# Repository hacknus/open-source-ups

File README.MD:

# Open Source UPS

[!CAUTION]
The BOOST circuit in rev 2 cannot provide sufficient current to start a HDD.

UPS are commonly used in server applications to protect against power outages. For home applications, for example to protect a NAS, small Uninterruptible Power Supplies (UPS) do exist, but they all lack the USB HID communication to shut down the NAS/Server/Host when the battery gets low.
For small scale applications like Synology NAS products that operate at 12V, there currently exists no UPS product that is able to buffer the power and communicate over USB when the battery level gets critically low.
Only high voltage solutions (110V or 230V) exist, which also include an inverter and are thus much less efficient and overpowered for a simple 12V Synology NAS.
This is a simple, open source UPS, based around an STM32F405 and written in Rust.

The USB HID communication is based on the great work done by [abratchik](https://github.com/abratchik) for the Arduino platform [here](https://github.com/abratchik/HIDPowerDevice/tree/master). 
The hardware is essentially just a charging circuit where the remaining capacity is monitored by the MCU.

## Hardware
Attention! This pcb does not contain a battery protection circuit - if you wish to implement one, just use the Keystone 1047 battery case instead of the Keystone 1048P and wire a breakout 2S BMS before connecting the batteries to the PCB.
The hardware can be found in the [hardware folder](hardware), containing step files for the case as well as EAGLE files for the PCB.

## Flashing the firmware
Easiest way to flash: Connect via USB-C to your computer. Press RESET and BOOT button on the back of the PCB, release RST first and then release BOOT. The device is now in DFU mode.

Then run the following:
```sh
cargo build --release
/usr/bin/arm-none-eabi-objcopy -O binary   target/thumbv7em-none-eabihf/release/open-source-ups   firmware.bin
dfu-util -l
dfu-util -d 0483:df11 -a 0 \
  -s 0x08000000:leave -D firmware.bin
```

Alternatively:
Connect the board using a ST-Link V3 (with TagConnect) to a USB port on the computer. Be sure to power the board with an
additional USB-C connector. (ST-Link does not provide power)  
First start the openocd server in a terminal/console window:
```openocd -f interface/stlink-v2-1.cfg -f target/stm32f4x.cfg```   
Flash/Run the code on the hardware using:  
```cargo run --release```  
note: release is important for USB to work reliably!

To set up your system, be sure to
follow [this guide](https://docs.rust-embedded.org/discovery/f3discovery/03-setup/index.html)!

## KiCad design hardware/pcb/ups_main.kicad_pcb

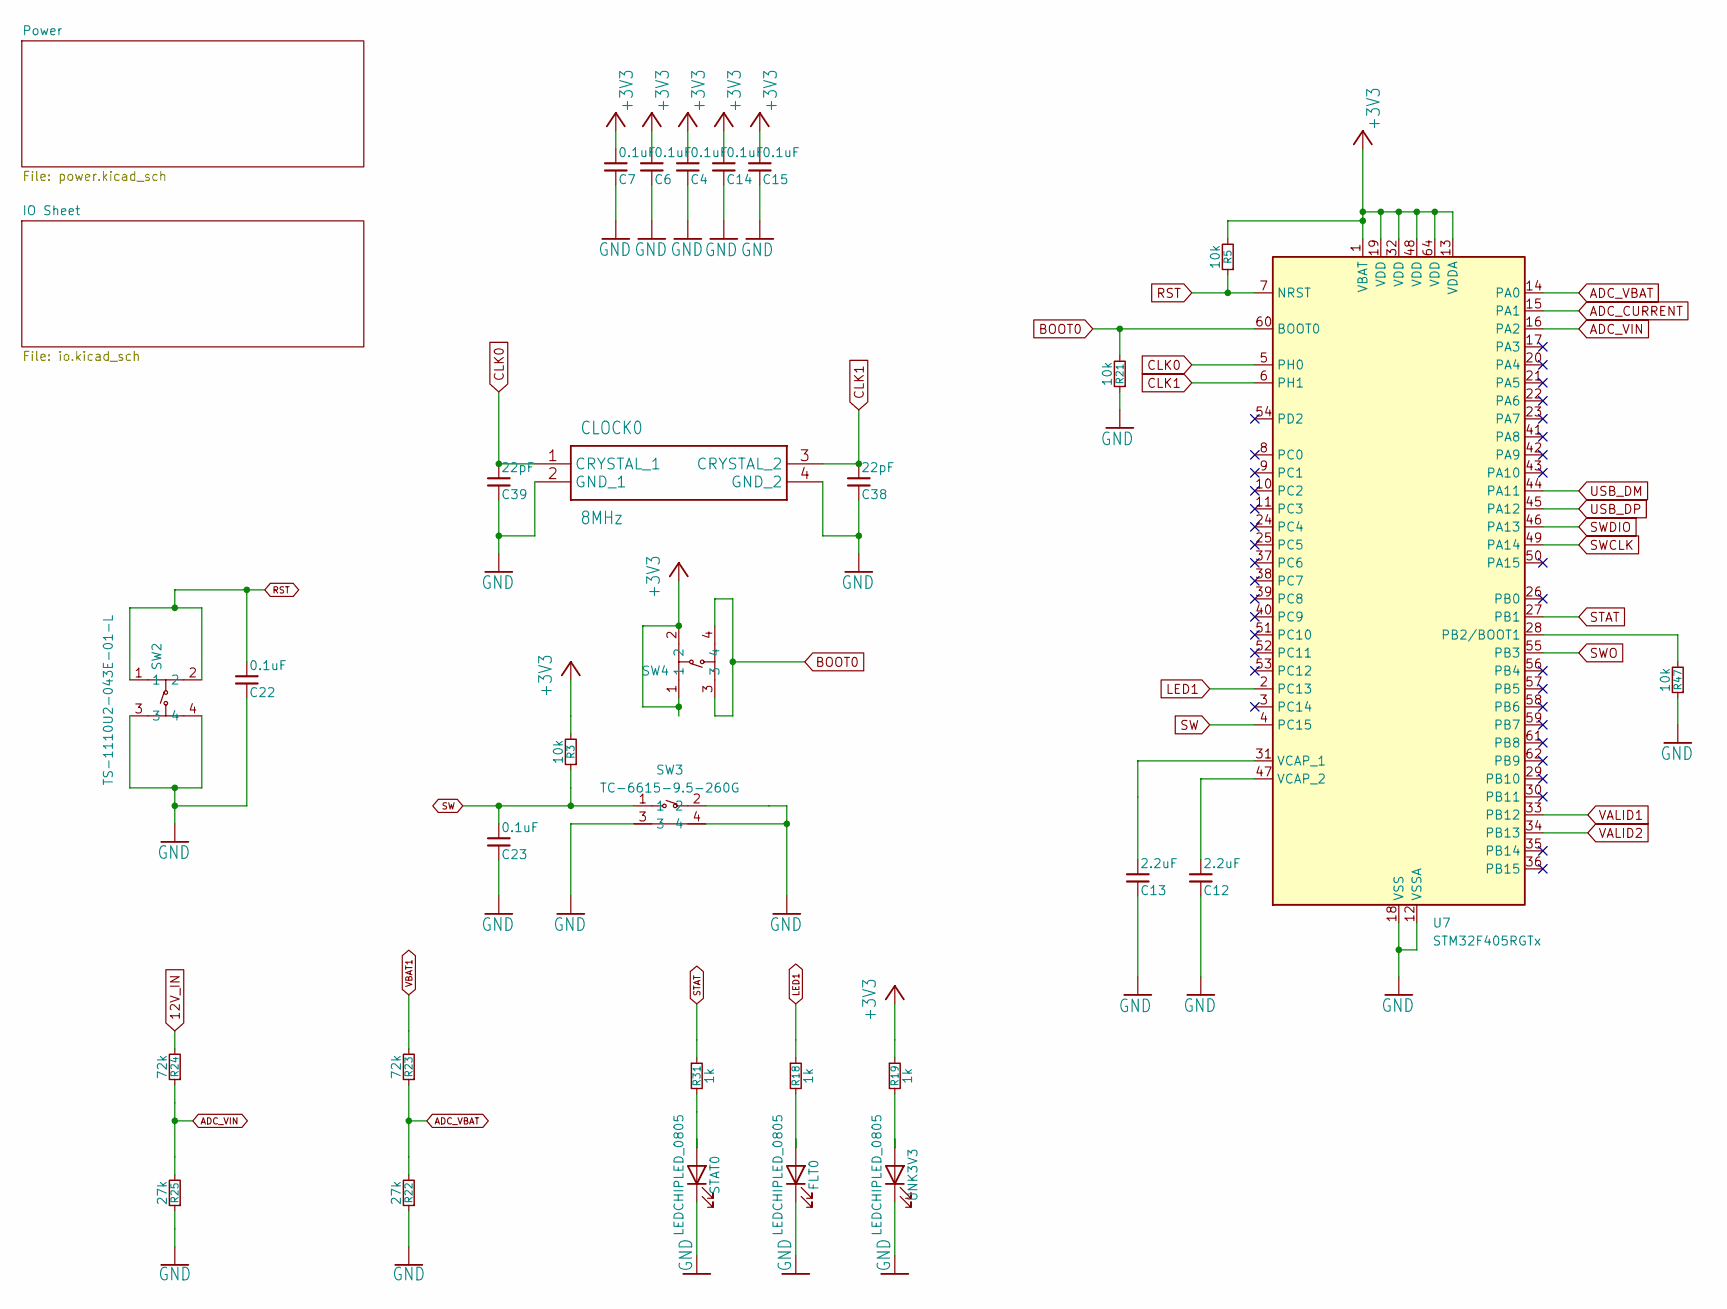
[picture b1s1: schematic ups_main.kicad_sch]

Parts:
C4, C6, C7, C14, C15, C22, C23: 0.1uF; C_0603_1608Metric_Pad1.08x0.95mm_HandSolder
C12, C13: 2.2uF; C_0603_1608Metric_Pad1.08x0.95mm_HandSolder
C38, C39: 22pF; C_0603_1608Metric_Pad1.08x0.95mm_HandSolder
CLOCK0: 8MHz; ABM8AIG8000MHZ1ZT; MANUFACTURER_PART_NUMBER ABM8AIG-8.000MHZ-1Z-T; MOUSER_PART_NUMBER 815-M8AIG-8-1ZT
FLT0: LEDCHIPLED_0805; LED_0805_2012Metric
R3, R5, R21, R47: 10k; R_0603_1608Metric_Pad0.98x0.95mm_HandSolder
R18, R19, R31: 1k; R_0603_1608Metric_Pad0.98x0.95mm_HandSolder
R22, R25: 27k; R_0603_1608Metric_Pad0.98x0.95mm_HandSolder
R23, R24: 72k; R_0603_1608Metric_Pad0.98x0.95mm_HandSolder
STAT0: LEDCHIPLED_0805; LED_0805_2012Metric
SW2, SW4: TS-1110U2-043E-01-L; SW-SMD_4P-L6.5-W6.5-P4.00-LS6.8; MPN TS-1110U2-043E-01-L; LCSC Part C25168654
SW3: TC-6615-9.5-260G; SW-TH_4P-L7.5-W9.5-P4.50; MPN TC-6615-9.5-260G; LCSC Part C2845278
U7: STM32F405RGTx; LQFP-64_10x10mm_P0.5mm
UNK3V3: LEDCHIPLED_0805; LED_0805_2012Metric

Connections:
12V_IN: R24.2; also elsewhere on the board
+3V3: C4.1, C6.1, C7.1, C14.1, C15.1, R3.2, R5.2, R19.1, SW4.1, SW4.2, U7.1 (VBAT), U7.13 (VDDA), U7.19 (VDD), U7.32 (VDD), U7.48 (VDD), U7.64 (VDD); also elsewhere on the board
ADC_CURRENT: U7.15 (PA1); also elsewhere on the board
ADC_VBAT: R22.2, R23.1, U7.14 (PA0)
ADC_VIN: R24.1, R25.2, U7.16 (PA2)
BOOT0: R21.2, SW4.3, SW4.4, U7.60 (BOOT0)
CLK0: C39.1, CLOCK0.1 (CRYSTAL_1), U7.5 (PH0)
CLK1: C38.1, CLOCK0.3 (CRYSTAL_2), U7.6 (PH1)
GND: C4.2, C6.2, C7.2, C12.2, C13.2, C14.2, C15.2, C22.2, C23.2, C38.2, C39.2, CLOCK0.2 (GND_1), CLOCK0.4 (GND_2), FLT0.1 (K), R21.1, R22.1, R25.1, R47.1, STAT0.1 (K), SW2.3, SW2.4, SW3.2, SW3.3, SW3.4, U7.12 (VSSA), U7.18 (VSS), U7.63 (VSS), UNK3V3.1 (K); also elsewhere on the board
LED1: R18.1, U7.2 (PC13)
unnamed: FLT0.2 (A), R18.2
unnamed: R31.2, STAT0.2 (A)
unnamed: R47.2, U7.28 (PB2/BOOT1)
unnamed: C13.1, U7.31 (VCAP_1)
unnamed: C12.1, U7.47 (VCAP_2)
unnamed: R19.2, UNK3V3.2 (A)
RST: C22.1, R5.1, SW2.1, SW2.2, U7.7 (NRST); also elsewhere on the board
STAT: R31.1, U7.27 (PB1)
SW: C23.1, R3.1, SW3.1, U7.4 (PC15)
SWCLK: U7.49 (PA14); also elsewhere on the board
SWDIO: U7.46 (PA13); also elsewhere on the board
SWO: U7.55 (PB3); also elsewhere on the board
USB_DM: U7.44 (PA11); also elsewhere on the board
USB_DP: U7.45 (PA12); also elsewhere on the board
VALID1: U7.33 (PB12); also elsewhere on the board
VALID2: U7.34 (PB13); also elsewhere on the board
VBAT1: R23.2; also elsewhere on the board

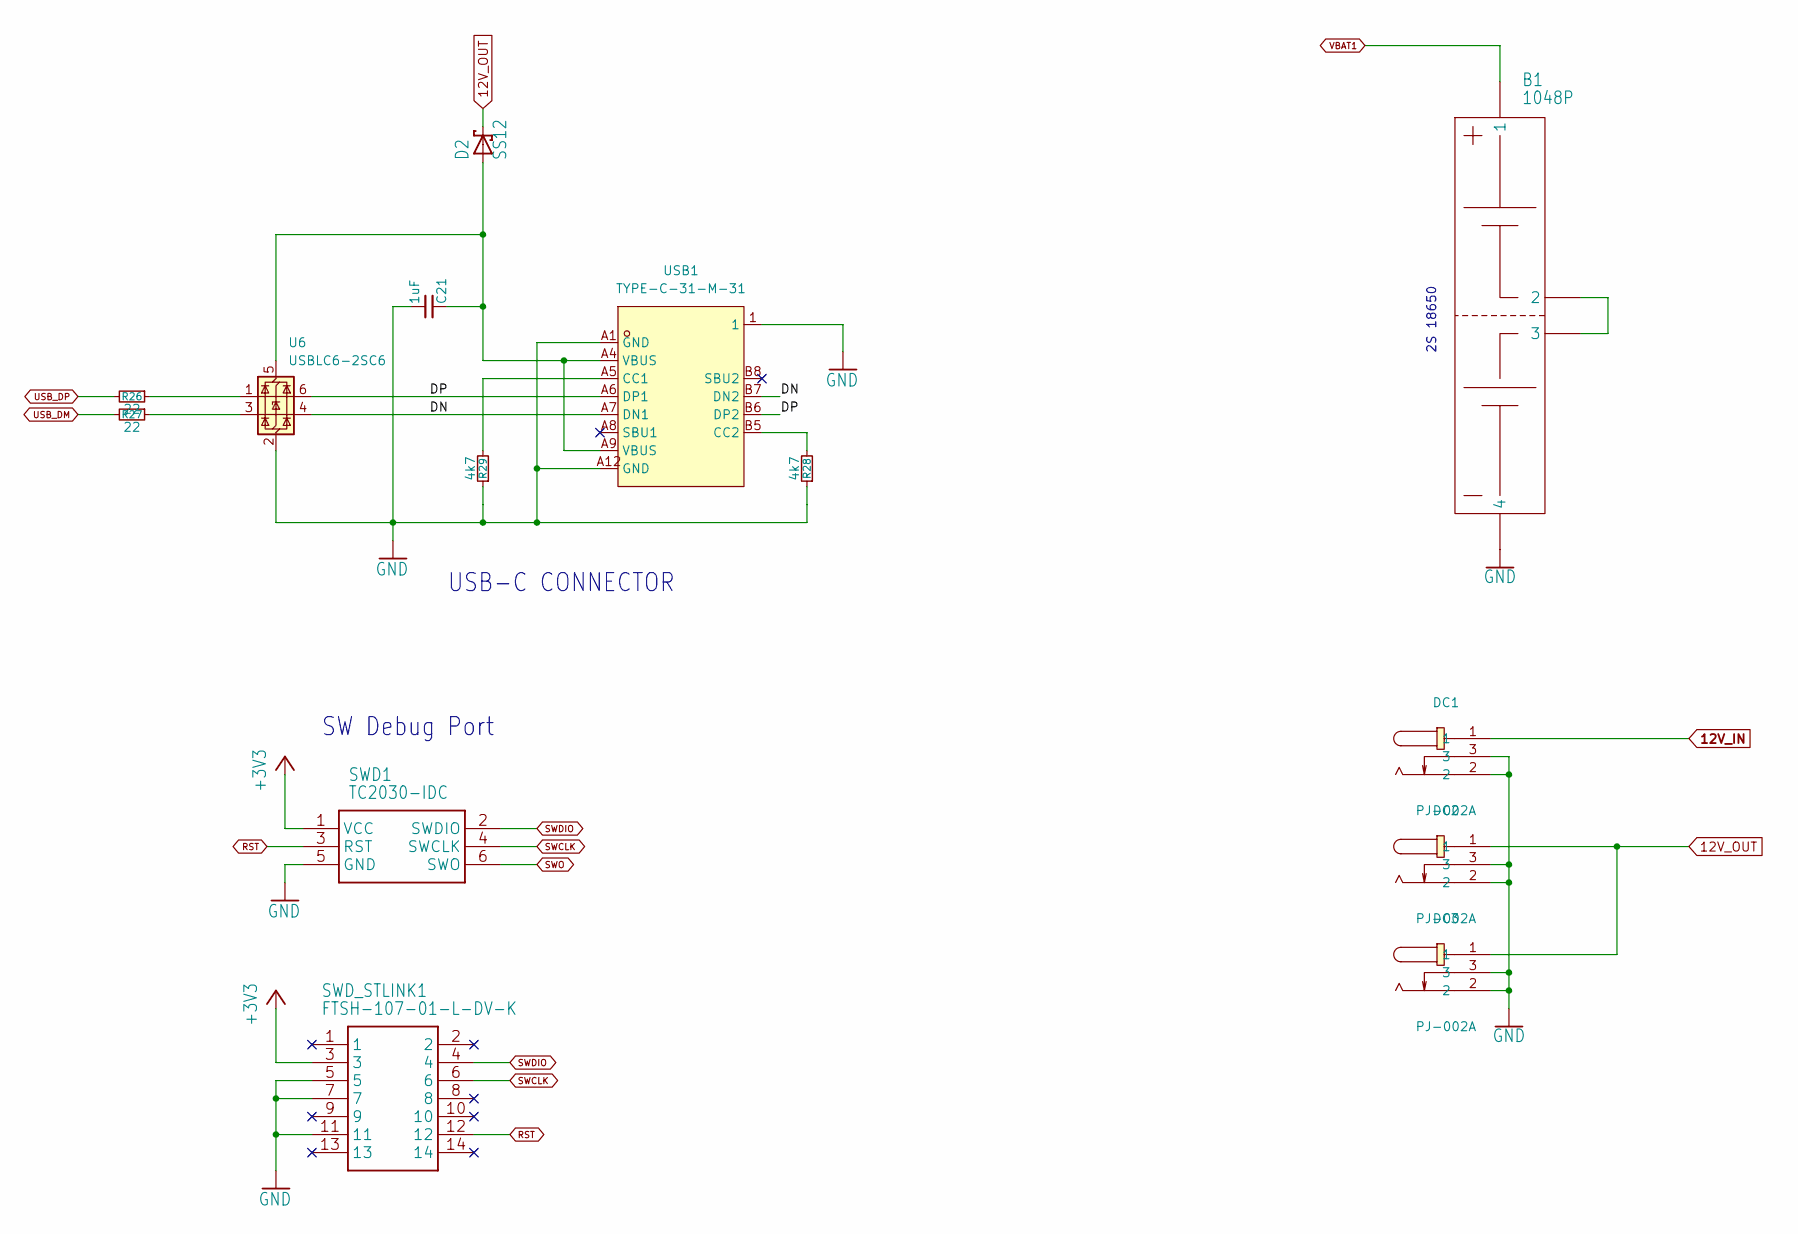
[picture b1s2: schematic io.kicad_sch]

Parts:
B1: 1048P; BATH_KEYSTONE_1048P; MANUFACTURER_PART_NUMBER 1048P; MOUSER_PART_NUMBER 534-1048P
C21: 1uF; C_0603_1608Metric_Pad1.08x0.95mm_HandSolder
D2: SS12; DO214AC
DC1, DC2, DC3: PJ-002A; DC-IN-TH_PJ-002A; MANUFACTURER_PART_NUMBER 694106301002; MOUSER_PART_NUMBER 710-694106301002
R26, R27: 22; R_0603_1608Metric_Pad0.98x0.95mm_HandSolder
R28, R29: 4k7; R_0603_1608Metric_Pad0.98x0.95mm_HandSolder
SWD1: TC2030-IDC; TC2030IDC; MANUFACTURER_PART_NUMBER TC2030-IDC
SWD_STLINK1: FTSH-107-01-L-DV-K; FTSH-107-XX-YYY-DV-K; MANUFACTURER_PART_NUMBER FTSH-107-01-L-DV-K; MOUSER_PART_NUMBER 200-FTSH10701LDVK
U6: USBLC6-2SC6; SOT-23-6
USB1: TYPE-C-31-M-31; USB-C-SMD_TYPE-C-31-M-31; MPN TYPE-C-31-M-31; LCSC Part C2760486

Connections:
12V_IN: DC1.1; also elsewhere on the board
12V_OUT: D2.C, DC2.1, DC3.1; also elsewhere on the board
+3V3: SWD1.1 (VCC), SWD_STLINK1.3; also elsewhere on the board
/IO Sheet/DN: U6.4 (I/O2), USB1.A7 (DN1), USB1.B7 (DN2)
/IO Sheet/DP: U6.6 (I/O1), USB1.A6 (DP1), USB1.B6 (DP2)
GND: B1.4, C21.1, DC1.2, DC1.3, DC2.2, DC2.3, DC3.2, DC3.3, R28.1, R29.1, SWD1.5 (GND), SWD_STLINK1.5, SWD_STLINK1.7, SWD_STLINK1.11, U6.2 (GND), USB1.1, USB1.A1 (GND), USB1.A12 (GND); also elsewhere on the board
unnamed: B1.2, B1.3
unnamed: R26.1, U6.1 (I/O1)
unnamed: R27.1, U6.3 (I/O2)
unnamed: C21.2, D2.A, U6.5 (VBUS), USB1.A4 (VBUS), USB1.A9 (VBUS)
unnamed: R29.2, USB1.A5 (CC1)
unnamed: R28.2, USB1.B5 (CC2)
RST: SWD1.3 (RST), SWD_STLINK1.12; also elsewhere on the board
SWCLK: SWD1.4 (SWCLK), SWD_STLINK1.6; also elsewhere on the board
SWDIO: SWD1.2 (SWDIO), SWD_STLINK1.4; also elsewhere on the board
SWO: SWD1.6 (SWO); also elsewhere on the board
USB_DM: R27.2; also elsewhere on the board
USB_DP: R26.2; also elsewhere on the board
VBAT1: B1.1; also elsewhere on the board

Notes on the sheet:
USB-C CONNECTOR
2S 18650
SW Debug Port

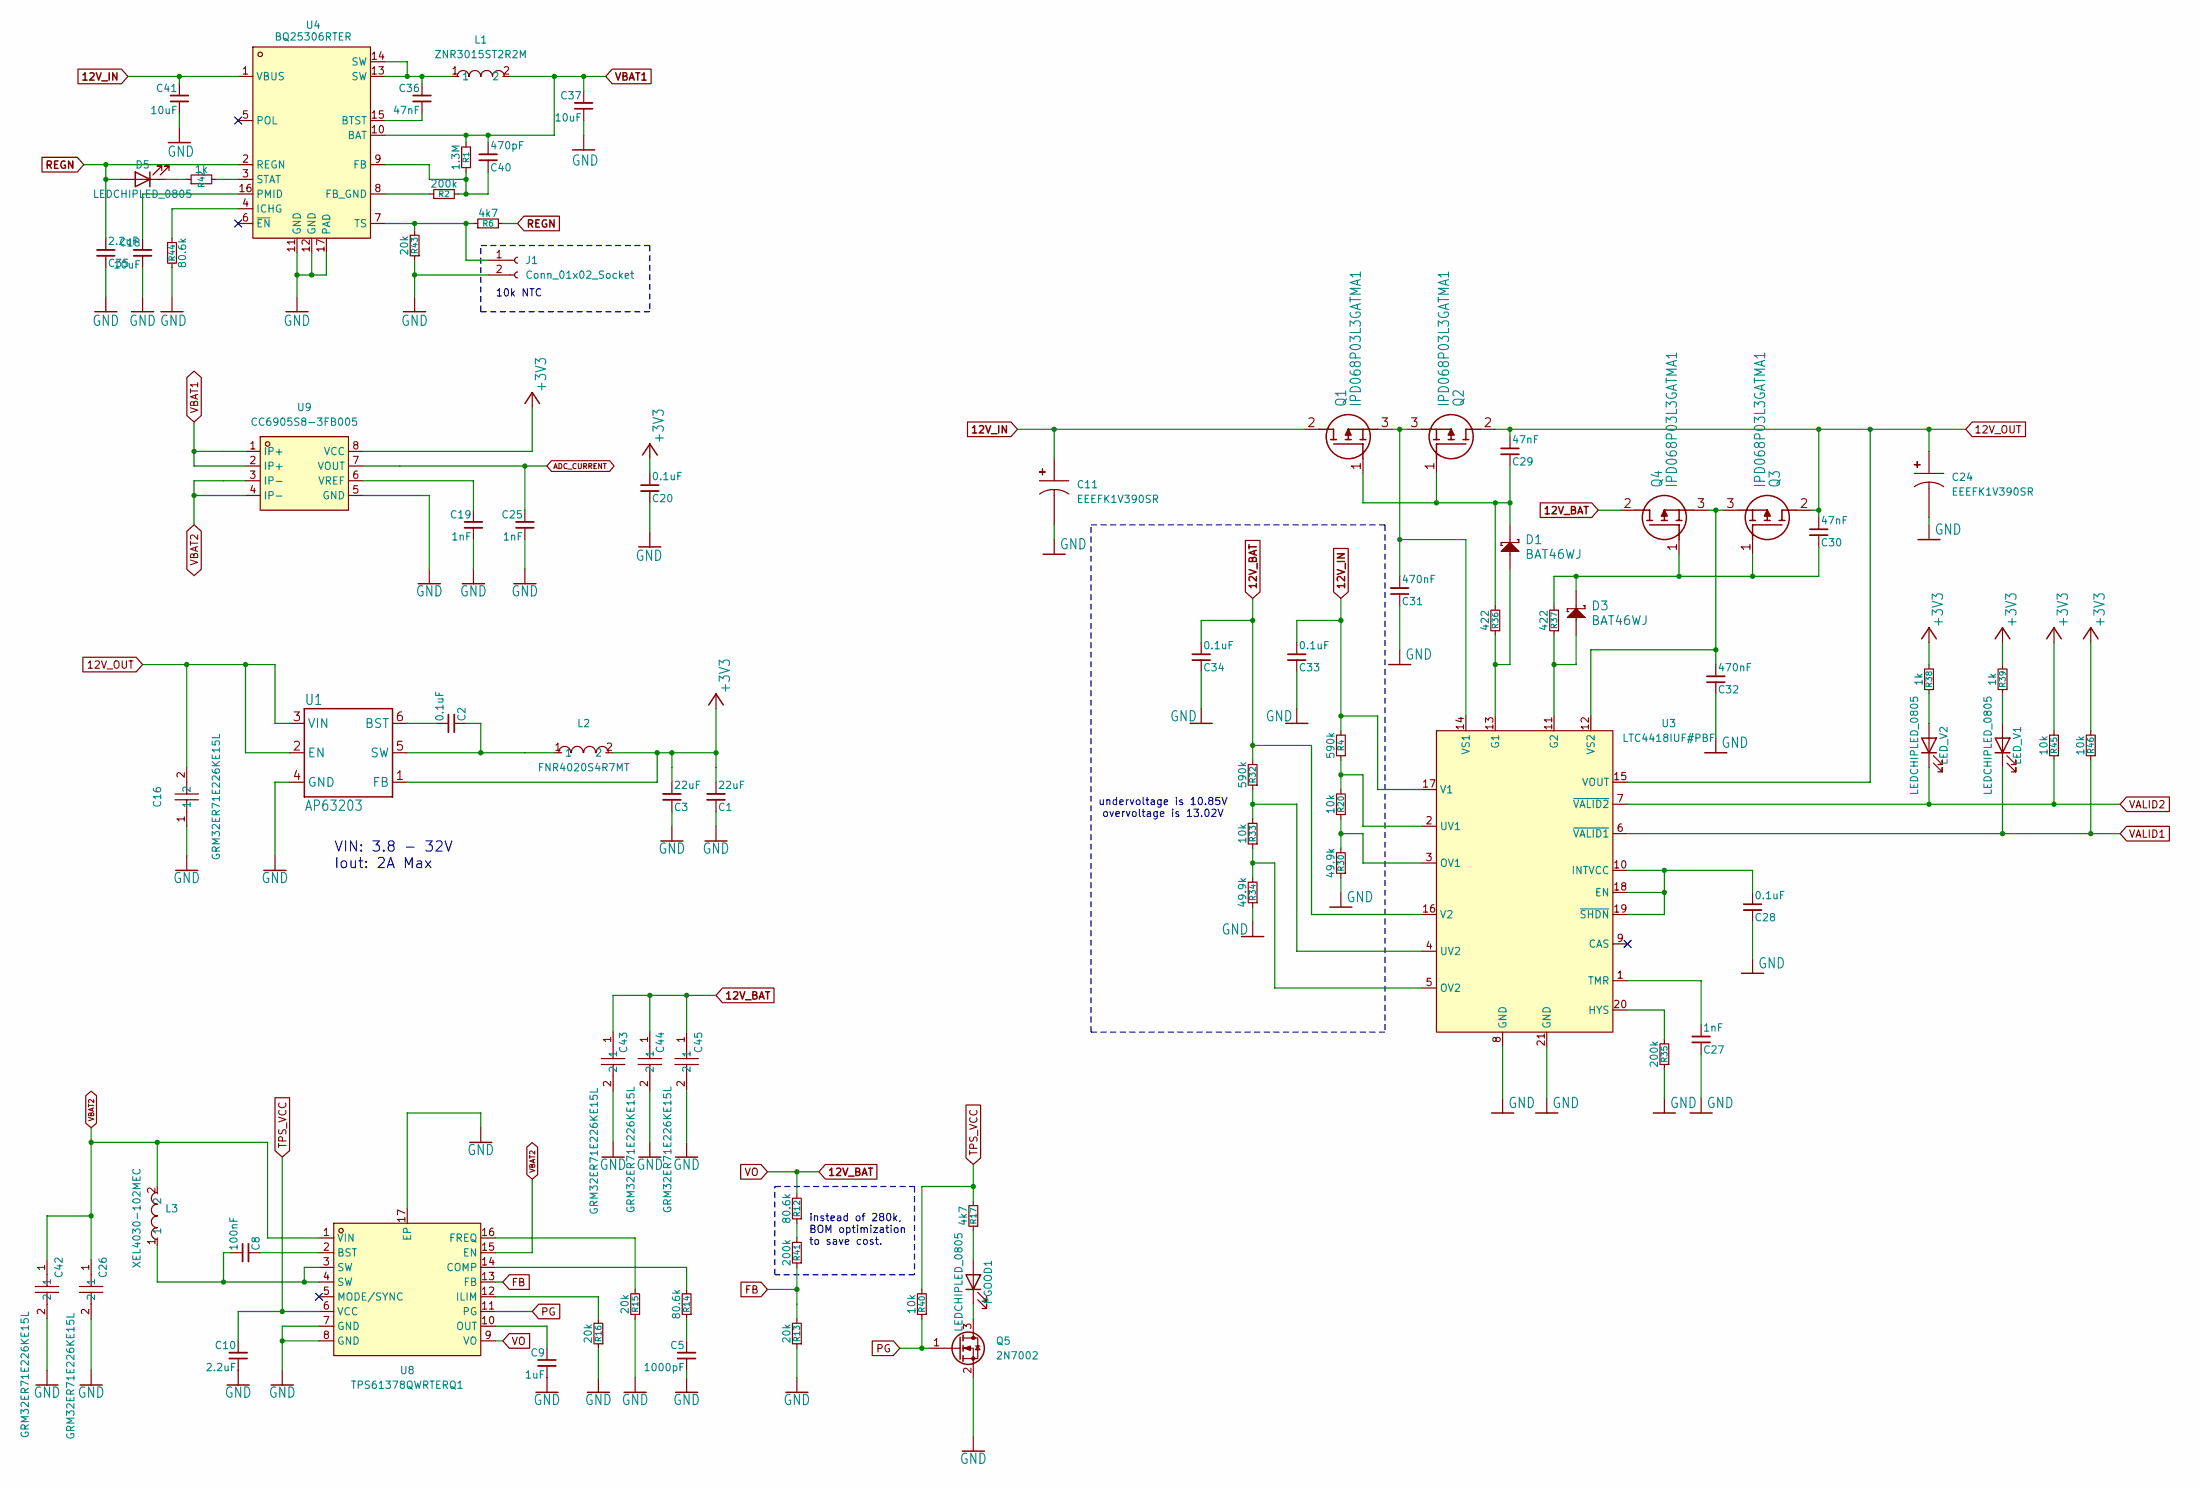
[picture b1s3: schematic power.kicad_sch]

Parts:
C1, C3: 22uF; C_0603_1608Metric_Pad1.08x0.95mm_HandSolder
C2, C20, C28, C33, C34: 0.1uF; C_0603_1608Metric_Pad1.08x0.95mm_HandSolder
C5: 1000pF; C_0603_1608Metric_Pad1.08x0.95mm_HandSolder
C8: 100nF; C_0603_1608Metric_Pad1.08x0.95mm_HandSolder
C9: 1uF; C_0603_1608Metric_Pad1.08x0.95mm_HandSolder
C10, C35: 2.2uF; C_0603_1608Metric_Pad1.08x0.95mm_HandSolder
C11, C24: EEEFK1V390SR; CAP-SMD_BD5.0-L5.3-W5.3-FD; MPN EEEFK1V390SR; LCSC Part C336803
C16, C26, C42, C43, C44, C45: GRM32ER71E226KE15L; C1210; MPN GRM32ER71E226KE15L; LCSC Part C21397
C18, C37, C41: 10uF; C_0603_1608Metric_Pad1.08x0.95mm_HandSolder
C19, C25, C27: 1nF; C_0603_1608Metric_Pad1.08x0.95mm_HandSolder
C29, C30, C36: 47nF; C_0603_1608Metric_Pad1.08x0.95mm_HandSolder
C31, C32: 470nF; C_0603_1608Metric_Pad1.08x0.95mm_HandSolder
C40: 470pF; C_0603_1608Metric_Pad1.08x0.95mm_HandSolder
D1, D3: BAT46WJ; SODFL2513X80N; Voltage 100V; Part Number BAT46WJ
D5: LEDCHIPLED_0805; LED_0805_2012Metric
J1: Conn_01x02_Socket; SolderWire-0.25sqmm_1x02_P4.2mm_D0.65mm_OD1.7mm
L1: ZNR3015ST2R2M; IND-SMD_L3.0-W3.0-1; MPN ZNR3015ST2R2M; LCSC Part C42429102
L2: FNR4020S4R7MT; IND-SMD_L4.0-W4.0_FNR40XXS; MANUFACTURER_PART_NUMBER MLZ2012M4R7HT000; MOUSER_PART_NUMBER 810-MLZ2012M4R7HT000
L3: XEL4030-102MEC; IND-SMD_L4.0-W4.0_XEL4030; MPN XEL4030-102MEC; LCSC Part C5441341
LED_V1, LED_V2: LEDCHIPLED_0805; LED_0805_2012Metric
PGOOD1: LEDCHIPLED_0805; LED_0805_2012Metric
Q1, Q2, Q3, Q4: IPD068P03L3GATMA1; MANUFACTURER_PART_NUMBER IPD068P03L3GATMA1; MOUSER_PART_NUMBER 726-IPD068P03L3GATMA
Q5: 2N7002; SOT-23
R1: 1.3M; R_0603_1608Metric_Pad0.98x0.95mm_HandSolder
R2, R35, R41: 200k; R_0603_1608Metric_Pad0.98x0.95mm_HandSolder
R4, R32: 590k; R_0603_1608Metric_Pad0.98x0.95mm_HandSolder
R6, R17: 4k7; R_0603_1608Metric_Pad0.98x0.95mm_HandSolder
R12, R14, R44: 80.6k; R_0603_1608Metric_Pad0.98x0.95mm_HandSolder
R13, R15, R16, R43: 20k; R_0603_1608Metric_Pad0.98x0.95mm_HandSolder
R20, R33, R40, R45, R46: 10k; R_0603_1608Metric_Pad0.98x0.95mm_HandSolder
R30, R34: 49.9k; R_0603_1608Metric_Pad0.98x0.95mm_HandSolder
R36, R37: 422; R_0603_1608Metric_Pad0.98x0.95mm_HandSolder
R38, R39, R42: 1k; R_0603_1608Metric_Pad0.98x0.95mm_HandSolder
U1: AP63203; SOT23-6
U3: LTC4418IUF#PBF; QFN-20_L4.0-W4.0-P0.50-BL-EP2.5; MPN LTC4418IUF#PBF; LCSC Part C580908
U4: BQ25306RTER; TQFN-16_L3.0-W3.0-P0.50-BL-EP1.7; MPN BQ25306RTER; LCSC Part C3682611
U8: TPS61378QWRTERQ1; WQFN-16_L3.0-W3.0-P0.50-TL-EP1.7; MPN TPS61378QWRTERQ1; LCSC Part C2861010
U9: CC6905S8-3FB005; SOIC-8_L4.9-W3.9-P1.27-LS6.0-BL; MPN CC6905S8-3FB005; LCSC Part C41421487

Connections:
12V_BAT: C34.1, C43.1, C44.1, C45.1, Q4.2 (D), R12.2, R32.2, U3.16 (V2), U8.9 (VO)
12V_IN: C11.1, C33.1, C41.2, Q1.2 (D), R4.2, U3.17 (V1), U4.1 (VBUS); also elsewhere on the board
12V_OUT: C16.2, C24.1, C29.1, C30.1, Q2.2 (D), Q3.2 (D), U1.2 (EN), U1.3 (VIN), U3.15 (VOUT); also elsewhere on the board
+3V3: C1.1, C3.1, C20.1, L2.2, R38.2, R39.2, R45.2, R46.2, U1.1 (FB), U9.8 (VCC); also elsewhere on the board
ADC_CURRENT: C25.2, U9.7 (VOUT); also elsewhere on the board
FB: R13.2, R41.1, U8.13 (FB)
GND: C1.2, C3.2, C5.1, C9.1, C10.1, C11.2, C16.1, C18.1, C19.1, C20.2, C24.2, C25.1, C26.2, C27.2, C28.2, C31.2, C32.2, C33.2, C34.2, C35.2, C37.1, C41.1, C42.2, C43.2, C44.2, C45.2, J1.2, Q5.2 (S), R13.1, R15.1, R16.1, R30.1, R34.1, R35.1, R43.1, R44.2, U1.4 (GND), U3.8 (GND), U3.21 (GND), U4.11 (GND), U4.12 (GND), U4.17 (PAD), U8.7 (GND), U8.8 (GND), U8.17 (EP), U9.5 (GND); also elsewhere on the board
unnamed: C5.2, R14.1
unnamed: C8.1, L3.1, U8.3 (SW), U8.4 (SW)
unnamed: C36.2, L1.1, U4.13 (SW), U4.14 (SW)
unnamed: D1.2 (A), R36.1, U3.13 (G1)
unnamed: C29.2, D1.1 (C), Q1.1 (G), Q2.1 (G), R36.2
unnamed: D3.2 (A), R37.1, U3.11 (G2)
unnamed: C30.2, D3.1 (C), Q3.1 (G), Q4.1 (G), R37.2
unnamed: D5.1 (K), R42.1
unnamed: J1.1, R6.1, R43.2, U4.7 (TS)
unnamed: LED_V1.2 (A), R39.1
unnamed: LED_V2.2 (A), R38.1
unnamed: PGOOD1.2 (A), R17.1
unnamed: PGOOD1.1 (K), Q5.3 (D)
unnamed: C31.1, Q1.3 (S), Q2.3 (S), U3.14 (VS1)
unnamed: C32.1, Q3.3 (S), Q4.3 (S), U3.12 (VS2)
unnamed: R12.1, R41.2
unnamed: C2.1, U1.6 (BST)
unnamed: C2.2, L2.1, U1.5 (SW)
unnamed: C28.1, U3.10 (INTVCC), U3.18 (EN), U3.19 (~SHDN)
unnamed: R35.2, U3.20 (HYS)
unnamed: R20.1, R30.2, U3.3 (OV1)
unnamed: R33.1, R34.2, U3.5 (OV2)
unnamed: C27.1, U3.1 (TMR)
unnamed: R4.1, R20.2, U3.2 (UV1)
unnamed: R32.1, R33.2, U3.4 (UV2)
unnamed: C36.1, U4.15 (BTST)
unnamed: C40.2, R1.1, R2.2, U4.9 (FB)
unnamed: R2.1, U4.8 (FB_GND)
unnamed: R44.1, U4.4 (ICHG)
unnamed: C18.2, U4.16 (PMID)
unnamed: R42.2, U4.3 (STAT)
unnamed: C8.2, U8.2 (BST)
unnamed: R14.2, U8.14 (COMP)
unnamed: R15.2, U8.16 (FREQ)
unnamed: R16.2, U8.12 (ILIM)
unnamed: C9.2, U8.10 (OUT)
unnamed: C19.2, U9.6 (VREF)
PG: Q5.1 (G), R40.1, U8.11 (PG)
REGN: C35.1, D5.2 (A), R6.2, U4.2 (REGN)
TPS_VCC: C10.2, R17.2, R40.2, U8.6 (VCC)
VALID1: LED_V1.1 (K), R46.1, U3.6 (~VALID1); also elsewhere on the board
VALID2: LED_V2.1 (K), R45.1, U3.7 (~VALID2); also elsewhere on the board
VBAT1: C37.2, C40.1, L1.2, R1.2, U4.10 (BAT), U9.1 (IP+), U9.2 (IP+); also elsewhere on the board
VBAT2: C26.1, C42.1, L3.2, U8.1 (VIN), U8.15 (EN), U9.3 (IP-), U9.4 (IP-)

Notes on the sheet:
instead of 280k, BOM optimization to save cost.
undervoltage is 10.85V overvoltage is 13.02V
10k NTC
VIN: 3.8 - 32V Iout: 2A Max

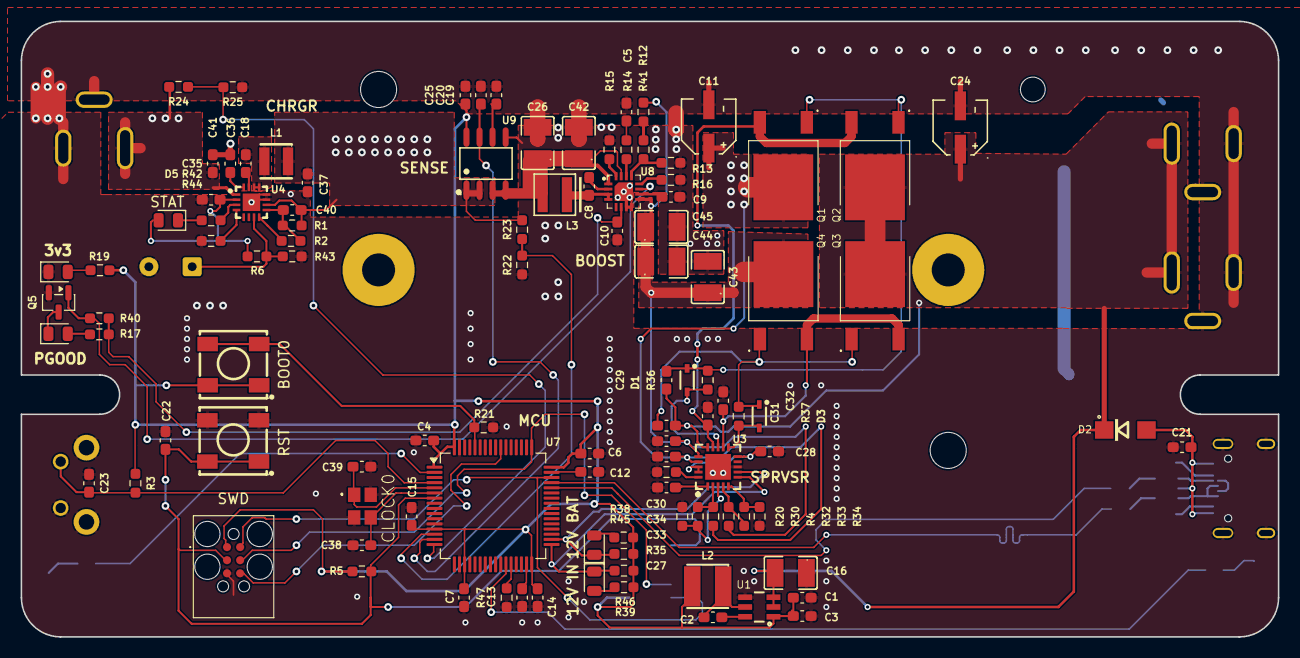
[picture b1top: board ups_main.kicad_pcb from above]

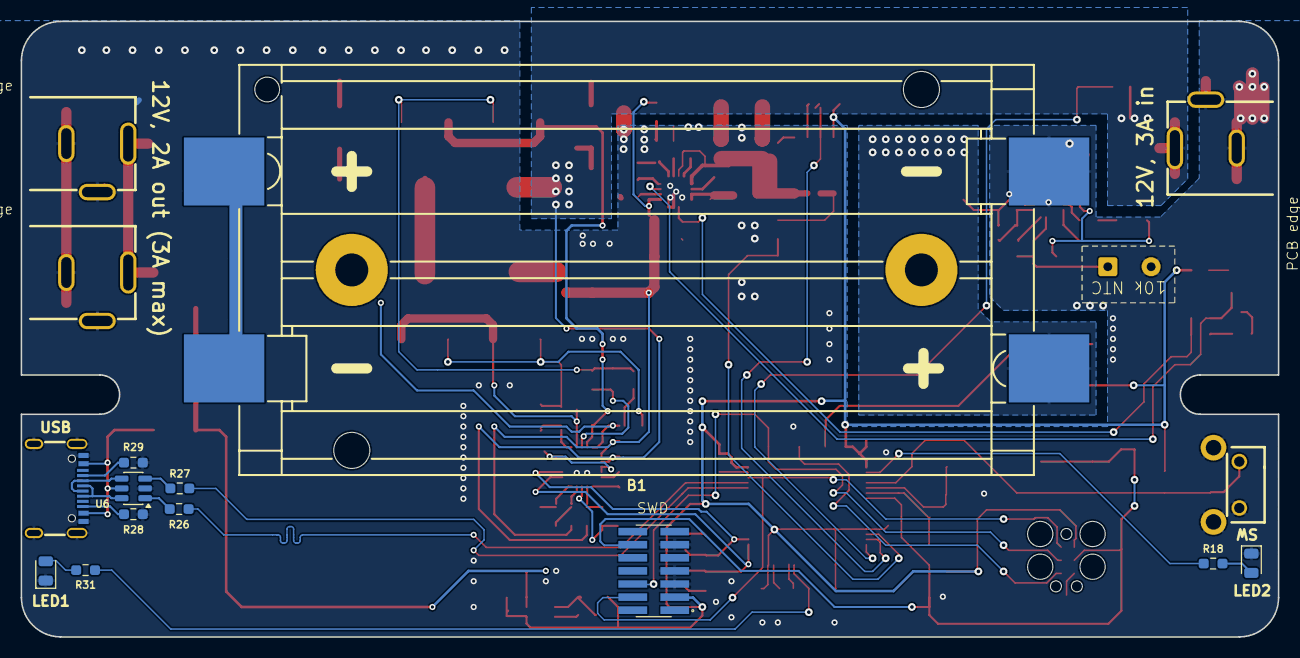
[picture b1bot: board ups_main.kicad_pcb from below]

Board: 2 copper layers, 121.9 x 59.7 mm, 123 parts (16 on the bottom side), 79 nets.

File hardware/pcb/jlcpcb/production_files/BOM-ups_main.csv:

Comment,Designator,Footprint,LCSC,Quantity
0.1uF,"C14,C15,C2,C20,C22,C23,C28,C33,C34,C4,C6,C7",C_0603_1608Metric_Pad1.08x0.95mm_HandSolder,C7501158,12
1.3M,R1,R_0603_1608Metric_Pad0.98x0.95mm_HandSolder,C103276,1
1000pF,C5,C_0603_1608Metric_Pad1.08x0.95mm_HandSolder,C1588,1
100nF,C8,C_0603_1608Metric_Pad1.08x0.95mm_HandSolder,C7501158,1
10k,"R20,R21,R3,R33,R40,R45,R46,R5",R_0603_1608Metric_Pad0.98x0.95mm_HandSolder,C108449,8
10uF,"C18,C37,C41",C_0603_1608Metric_Pad1.08x0.95mm_HandSolder,C96446,3
1k,"R18,R19,R31,R38,R39,R42",R_0603_1608Metric_Pad0.98x0.95mm_HandSolder,C2907002,6
1nF,"C19,C25,C27",C_0603_1608Metric_Pad1.08x0.95mm_HandSolder,C1588,3
1uF,"C21,C9",C_0603_1608Metric_Pad1.08x0.95mm_HandSolder,C108463,2
2.2uF,"C10,C12,C13,C35",C_0603_1608Metric_Pad1.08x0.95mm_HandSolder,C5360821,4
200k,"R2,R35,R41",R_0603_1608Metric_Pad0.98x0.95mm_HandSolder,C100847,3
20k,"R13,R15,R16,R43",R_0603_1608Metric_Pad0.98x0.95mm_HandSolder,C4184,4
22,"R26,R27",R_0603_1608Metric_Pad0.98x0.95mm_HandSolder,C23345,2
22pF,"C38,C39",C_0603_1608Metric_Pad1.08x0.95mm_HandSolder,C1653,2
22uF,"C1,C3",C_0603_1608Metric_Pad1.08x0.95mm_HandSolder,C20416425,2
27k,"R22,R25",R_0603_1608Metric_Pad0.98x0.95mm_HandSolder,C22967,2
2N7002,Q5,SOT-23,C916396,1
422,"R36,R37",R_0603_1608Metric_Pad0.98x0.95mm_HandSolder,C23052,2
470nF,"C31,C32",C_0603_1608Metric_Pad1.08x0.95mm_HandSolder,C152898,2
470pF,C40,C_0603_1608Metric_Pad1.08x0.95mm_HandSolder,C129628,1
47nF,"C29,C30,C36",C_0603_1608Metric_Pad1.08x0.95mm_HandSolder,C354390,3
49.9k,"R30,R34",R_0603_1608Metric_Pad0.98x0.95mm_HandSolder,C23184,2
4k7,"R17,R28,R29,R6",R_0603_1608Metric_Pad0.98x0.95mm_HandSolder,C163914,4
590k,"R32,R4",R_0603_1608Metric_Pad0.98x0.95mm_HandSolder,C103734,2
72k,"R23,R24",R_0603_1608Metric_Pad0.98x0.95mm_HandSolder,C2828635,2
80.6k,"R12,R14,R44",R_0603_1608Metric_Pad0.98x0.95mm_HandSolder,C101199,3
8MHz,CLOCK0,ABM8AIG8000MHZ1ZT,C5181478,1
AP63203,U1,SOT23-6,C780769,1
BAT46WJ,"D1,D3",SODFL2513X80N,C42407628,2
BQ25306RTER,U4,TQFN-16_L3.0-W3.0-P0.50-BL-EP1.7,C3682611,1
CC6905S8-3FB005,U9,SOIC-8_L4.9-W3.9-P1.27-LS6.0-BL,C41421487,1
EEEFK1V390SR,"C11,C24",CAP-SMD_BD5.0-L5.3-W5.3-FD,C336803,2
FNR4020S4R7MT,L2,IND-SMD_L4.0-W4.0_FNR40XXS,C167828,1
GRM32ER71E226KE15L,"C16,C26,C42,C43,C44,C45",C1210,C21397,6
IPD068P03L3GATMA1,"Q1,Q2,Q3,Q4",IPD068P03L3GATMA1,C42401094,4
LEDCHIPLED_0805,"FLT0,STAT0",LED_0805_2012Metric,C25170729,2
LEDCHIPLED_0805,"D5,LED_V1,LED_V2,PGOOD1,UNK3V3",LED_0805_2012Metric,C434437,5
LTC4418IUF#PBF,U3,QFN-20_L4.0-W4.0-P0.50-BL-EP2.5,C688512,1
PJ-002A,"DC1,DC2,DC3",DC-IN-TH_PJ-002A,C3096082,3
SS12,D2,DO214AC,C54426149,1
STM32F405RGTx,U7,LQFP-64_10x10mm_P0.5mm,C15742,1
TC-6615-9.5-260G,SW3,SW-TH_4P-L7.5-W9.5-P4.50,C2845278,1
TPS61378QWRTERQ1,U8,WQFN-16_L3.0-W3.0-P0.50-TL-EP1.7,C2861010,1
TS-1110U2-043E-01-L,"SW2,SW4",SW-SMD_4P-L6.5-W6.5-P4.00-LS6.8,C25168654,2
TYPE-C-31-M-31,USB1,USB-C-SMD_TYPE-C-31-M-31,C2760486,1
USBLC6-2SC6,U6,SOT-23-6,C5261088,1
XEL4030-102MEC,L3,IND-SMD_L4.0-W4.0_XEL4030,C5441341,1
ZNR3015ST2R2M,L1,IND-SMD_L3.0-W3.0-1,C42429102,1
10k,R47,R_0603_1608Metric_Pad0.98x0.95mm_HandSolder,,1

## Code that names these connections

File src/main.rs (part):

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    // initialize dma
    let dma2 = StreamsTuple::new(dp.DMA2);

    // U7 PB12/PB13 (pins 33/34): active-low LTC4418 VALID1/VALID2.
    // R46/R45 provide external pull-ups to 3.3 V.
    let valid1 = gpiob.pb12.into_floating_input();
    let valid2 = gpiob.pb13.into_floating_input();

    // U7 PB1 (pin 27): STAT, TIM3 channel 4.
    let led_dim = Channel4::new(gpiob.pb1);

    // U7 PC13 (pin 2): LED1.
    let mut usb_led1 = LED::new(gpioc.pc13.into_push_pull_output());

    // initialize pwm timer 3
    let mut stat_led_pwm = dp.TIM3.pwm_hz(led_dim, 10000.Hz(), &clocks).split();

    // U7 PA0/PA1/PA2 (pins 14/15/16): ADC_VBAT/ADC_CURRENT/ADC_VIN.

    let adc_vbat = gpioa.pa0.into_analog();
    let adc_current = gpioa.pa1.into_analog();
    let adc_vin = gpioa.pa2.into_analog();

    let dma_config = DmaConfig::default()
        .transfer_complete_interrupt(true)
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    }
    adc::start_scan();

    // U7 PC15 (pin 4): SW; the board provides the external pull-up.
    let sw = gpioc.pc15.into_floating_input();
    // U7 PA11/PA12 (pins 44/45): USB_DM/USB_DP.
    let usb = USB {
        usb_global: dp.OTG_FS_GLOBAL,
        usb_device: dp.OTG_FS_DEVICE,
        usb_pwrclk: dp.OTG_FS_PWRCLK,
        pin_dm: stm32f4xx_hal::gpio::alt::otg_fs::Dm::PA11(gpioa.pa11.into_alternate()),
        pin_dp: stm32f4xx_hal::gpio::alt::otg_fs::Dp::PA12(gpioa.pa12.into_alternate()),
        hclk: clocks.hclk(),
    };
    delay.delay(100.millis());
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    let initial_sample = adc::measurements(&mut last_sequence);
    let hid_mode = sw.is_high();
    usb::init(usb, hid_mode);
    let initial_source = PowerSource::from_pin_levels(valid1.is_high(), valid2.is_high());
    usb::update(battery.update(initial_source, initial_sample), true);
    unsafe {
        cortex_m::peripheral::NVIC::unmask(Interrupt::OTG_FS);
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                }
                adc::start_scan();
                if tick % 25 == 0 {
                    let source = PowerSource::from_pin_levels(valid1.is_high(), valid2.is_high());
                    let sample = if age < 50 { latest } else { None };
                    let telemetry = battery.update(source, sample);
                    usb::update(telemetry, tick == 0);
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
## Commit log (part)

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2024-08-11 test USB HID
2024-08-12 HID usb.rs
2024-08-12 change vid/pid and descriptor
2024-08-12 testing battery level reporting
2024-08-12 delay out of loop
2024-08-12 change delay
2024-08-12 capacity to u8
2024-08-12 try this
2024-08-12 struct
2024-08-12 long descriptor
2024-08-13 reporting in usb interrupt
2024-08-13 use different library
2024-08-14 send more information in report
2024-08-14 increase report count
2024-08-14 undo report size change
2024-08-14 send three reports
2024-08-14 this somehow did shut down the NAS
2024-08-14 use bitfields
2024-08-14 cleanup
2024-08-14 set status variables
2024-08-14 working UPS with synology
2024-08-14 fix reports
2024-08-14 include dummy logic
2024-09-27 add hardware files
2024-09-30 implemented IO pins
2024-09-30 slow sine for LED implemented
2024-10-01 update schem
2024-10-01 change name of USB dev
2024-10-01 add BMS note
2024-10-26 fix errors in schem/layout
2024-10-27 fix pgood led
2024-10-28 change led blink speed when power supply is disconnected
2024-10-28 fix adc
2024-10-28 fix voltage reading
2024-10-28 switch battery and ac present flags
2024-10-29 implement usb serial for debugging
2024-10-29 include usb interrupt for serial
2024-10-30 no charging might trigger shutdown
2024-10-30 minutes to seconds
2024-10-30 working version with synology
2026-04-29 Update README with caution about PCB design error
    Added caution note about PCB design error.
